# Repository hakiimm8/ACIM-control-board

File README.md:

# ACIM-control-board
 AC induction motor control board

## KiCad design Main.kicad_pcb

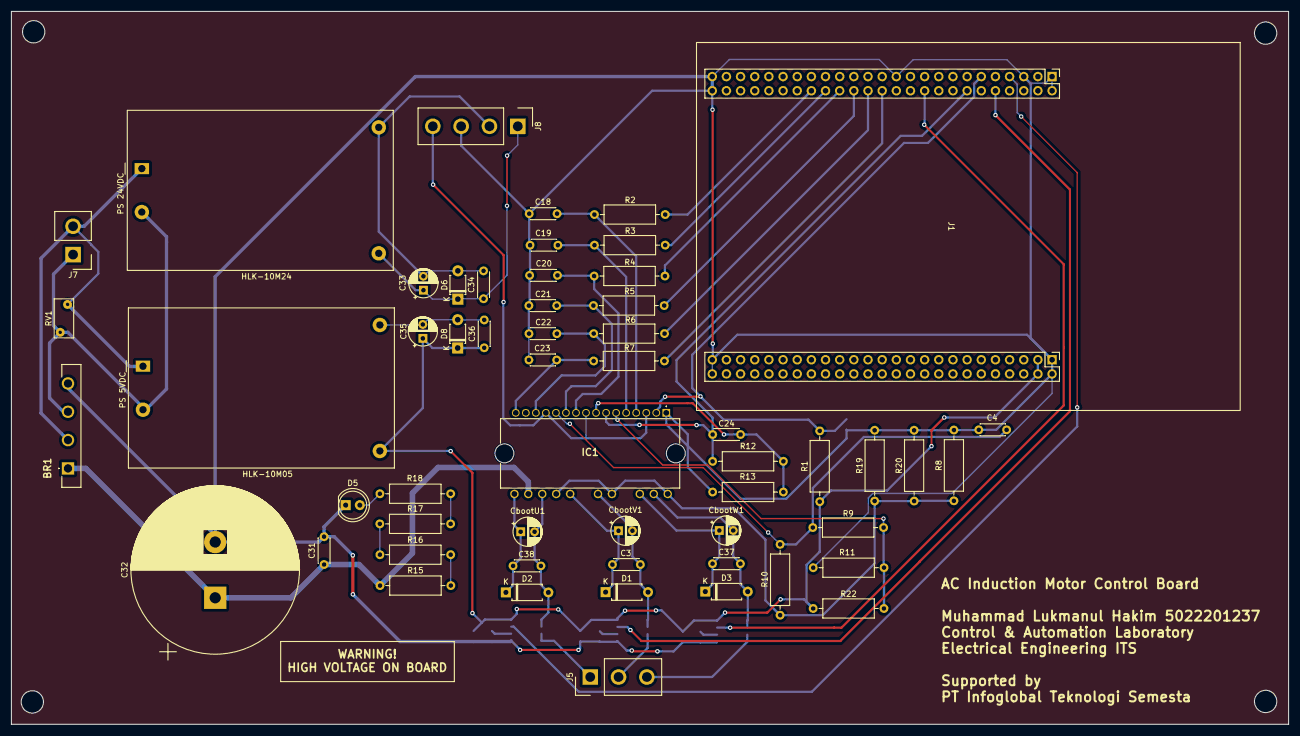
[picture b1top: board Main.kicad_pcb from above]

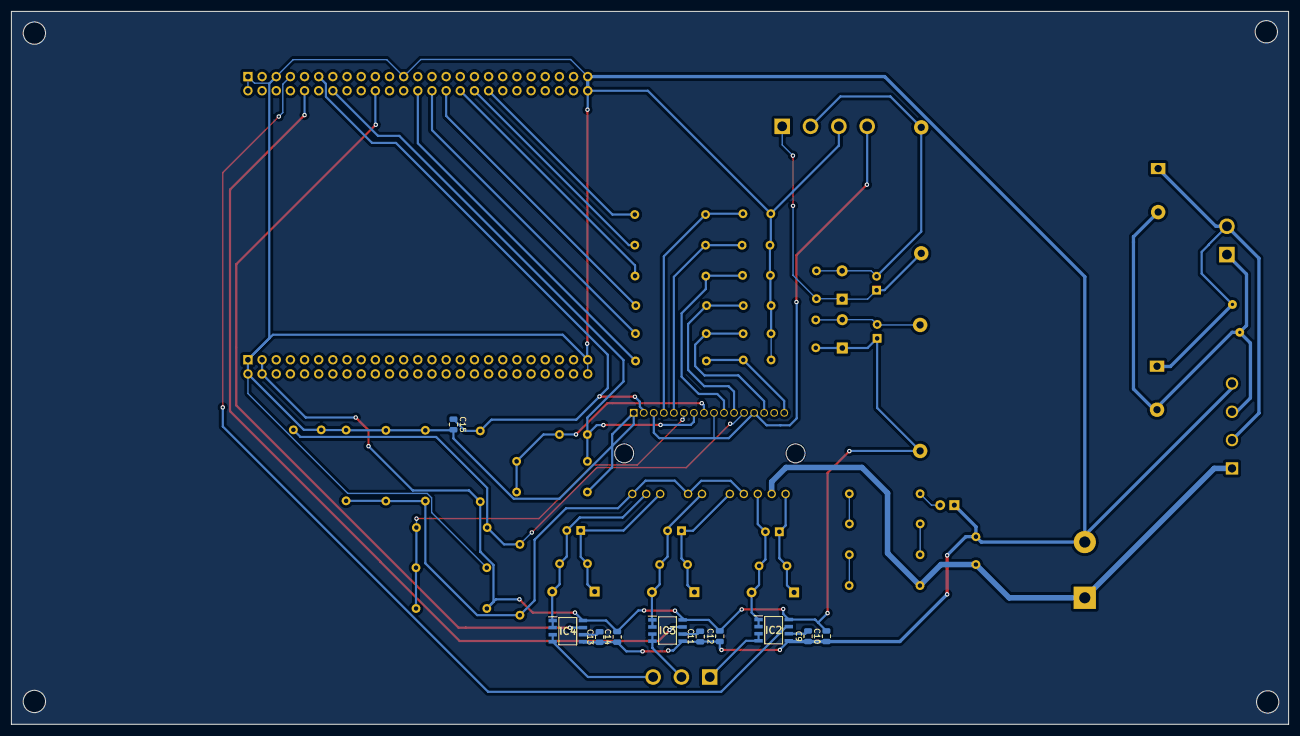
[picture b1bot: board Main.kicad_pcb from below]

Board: 2 copper layers, 229.1 x 127.9 mm, 65 parts (10 on the bottom side), 46 nets.

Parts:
BR1: GBUE2560-M3_P; GBUE2560M3P
C3, C37, C38: 100n; C_Disc_D4.3mm_W1.9mm_P5.00mm
C4: 1nF; C_Disc_D4.3mm_W1.9mm_P5.00mm
C9, C11, C13, C15: 1nF; C_0805_2012Metric
C10, C12, C14: 0.1uF; C_0805_2012Metric
C18, C19, C20, C21, C22, C23: 10pF; C_Disc_D4.3mm_W1.9mm_P5.00mm
C24: 33pF; C_Disc_D4.3mm_W1.9mm_P5.00mm
C31: 220nF; C_Disc_D4.3mm_W1.9mm_P5.00mm
C32: 330uF 400V; CP_Radial_D30.0mm_P10.00mm_SnapIn
C33, C35: 22uF; CP_Radial_D5.0mm_P2.50mm
C34, C36: 100nF; C_Disc_D4.3mm_W1.9mm_P5.00mm
CbootU1: 2.2u; CP_Radial_D5.0mm_P2.50mm
CbootV1: 2.2u; CP_Radial_D5.0mm_P2.50mm
CbootW1: 2.2u; CP_Radial_D5.0mm_P2.50mm
D1, D2, D3: MMSZ5250B; D_A-405_P7.62mm_Horizontal
D5: LED; LED_D5.0mm
D6: DZ24V; D_T-1_P5.08mm_Horizontal
D8: DZ5V; D_T-1_P5.08mm_Horizontal
IC1: STGIPQ3H60T-HL; STGIPQ3H60THL
IC2, IC3, IC4: ACS724LLCTR-05AU-T; SOIC127P600X175-8N
J1: STM32F407G-DISC1-SHIELD
J5: OUT; Samtec_HPM-03-01-x-S_Straight_1x03_Pitch5.08mm
J7: AC_IN; Samtec_HPM-02-01-x-S_Straight_1x02_Pitch5.08mm
J8: Conn_01x04; Samtec_HPM-04-01-x-S_Straight_1x04_Pitch5.08mm
PS 5VDC: HLK-10M05; Converter_ACDC_HiLink_HLK-10Mxx
PS 24VDC: HLK-10M24; Converter_ACDC_HiLink_HLK-10Mxx
R1: 2.2K; R_Axial_DIN0309_L9.0mm_D3.2mm_P12.70mm_Horizontal
R2, R3, R4, R5, R6, R7: 1K; R_Axial_DIN0309_L9.0mm_D3.2mm_P12.70mm_Horizontal
R8, R19, R20: 1R; R_Axial_DIN0309_L9.0mm_D3.2mm_P12.70mm_Horizontal
R9, R10, R11, R13, R22: 3.3K; R_Axial_DIN0309_L9.0mm_D3.2mm_P12.70mm_Horizontal
R12, R15, R16, R17, R18: 10K; R_Axial_DIN0309_L9.0mm_D3.2mm_P12.70mm_Horizontal
RV1: Varistor; RV_Disc_D7mm_W3.5mm_P5mm

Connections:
+5V: C10.2, C12.2, C14.2, C35.1, C36.1, D8.1 (K), IC2.8 (VCC), IC3.8 (VCC), IC4.8 (VCC), J1.53 (5V), J1.54 (5V), PS 5VDC.4 (+Vout), R1.1, R22.1
+15V: IC1.3 (VCC_W_), IC1.9 (VCC_V), IC1.13 (VCC_U), J8.4
+24V: C33.1, C34.1, D6.1 (K), J8.1, PS 24VDC.4 (+Vout)
/Inverter/ADC: C24.1, IC1.7 (OPOUT), J1.14 (PA2), R12.1
/Inverter/CURR_U: IC2.7 (VIOUT), J1.7 (PC1)
/Inverter/CURR_V: IC3.7 (VIOUT), J1.10 (PC2)
/Inverter/CURR_W: IC4.7 (VIOUT), J1.20 (PC4)
/Inverter/HIN_U: J1.28 (PE10), R6.1
/Inverter/HIN_V: J1.32 (PE14), R4.1
/Inverter/HIN_W: J1.36 (PB12), R2.1
/Inverter/HV: BR1.1 (+), C31.1, C32.1, IC1.18, R15.1
/Inverter/LIN_U: J1.26 (PE8), R7.1
/Inverter/LIN_V: J1.30 (PE12), R5.1
/Inverter/LIN_W: J1.34 (PB10), R3.1
/Inverter/NTC: C15.1, IC1.2 (T/~SD/OD_), J1.11 (PA1), R1.2
/Inverter/U: IC2.3 (IP-_1), IC2.4 (IP-_2), J5.1
/Inverter/V: IC3.3 (IP-_1), IC3.4 (IP-_2), J5.2
/Inverter/W: IC4.3 (IP-_1), IC4.4 (IP-_2), J5.3
/Rectifier & Power supply/L: BR1.2 (~_1), J7.2, PS 5VDC.1 (AC/L), PS 24VDC.1 (AC/L), RV1.1
/Rectifier & Power supply/N: BR1.3 (~_2), J7.1, PS 5VDC.2 (AC/N), PS 24VDC.2 (AC/N), RV1.2
GND: BR1.4 (-), C4.2, C9.1, C10.1, C11.1, C12.1, C13.1, C14.1, C15.2, C18.2, C19.2, C20.2, C21.2, C22.2, C23.2, C31.2, C32.2, D5.1 (K), IC1.1 (GND), IC2.5 (GND), IC3.5 (GND), IC4.5 (GND), J1.1 (GND), J1.2 (GND), J1.5 (GND), J1.23 (GND), J1.49 (GND), J1.50 (GND), J1.51 (GND), J1.52 (GND), J1.99 (GND), J1.100 (GND), J8.3, R8.2, R11.2, R13.2, R19.2, R20.2
unnamed: C3.1, CbootV1.2, D1.2 (A), IC1.22 (V_OUTV), IC3.1 (IP+_1), IC3.2 (IP+_2)
unnamed: C3.2, CbootV1.1, D1.1 (K), IC1.21 (VBOOT_V)
unnamed: C38.1, CbootU1.2, D2.2 (A), IC1.19 (U_OUTU), IC2.1 (IP+_1), IC2.2 (IP+_2)
unnamed: C38.2, CbootU1.1, D2.1 (K), IC1.17 (VBOOT_U)
unnamed: C37.1, CbootW1.2, D3.2 (A), IC1.25 (W_OUTW), IC4.1 (IP+_1), IC4.2 (IP+_2)
unnamed: C37.2, CbootW1.1, D3.1 (K), IC1.24 (VBOOT_W)
unnamed: D5.2 (A), R18.2
unnamed: C33.2, C34.2, D6.2 (A), J8.2, PS 24VDC.3 (-Vout)
unnamed: C35.2, C36.2, D8.2 (A), PS 5VDC.3 (-Vout)
unnamed: C22.1, IC1.14 (HIN_U), R6.2
unnamed: C20.1, IC1.10 (HIN_V_), R4.2
unnamed: C18.1, IC1.4 (HIN_W), R2.2
unnamed: C23.1, IC1.16 (LIN_U), R7.2
unnamed: C21.1, IC1.11 (LIN_V), R5.2
unnamed: C19.1, IC1.5 (LIN_W), R3.2
unnamed: IC1.20 (NU), IC1.23 (NV), IC1.26 (NW), R8.1, R10.2, R19.1, R20.1
unnamed: IC1.6 (OP+), R9.2, R11.1, R22.2
unnamed: C24.2, IC1.8 (OP-), R12.2, R13.1
unnamed: C9.2, IC2.6 (FILTER)
unnamed: C11.2, IC3.6 (FILTER)
unnamed: C13.2, IC4.6 (FILTER)
unnamed: R15.2, R16.1
unnamed: R16.2, R17.1
unnamed: R17.2, R18.1
RS: C4.1, IC1.12 (CIN_), R9.1, R10.1

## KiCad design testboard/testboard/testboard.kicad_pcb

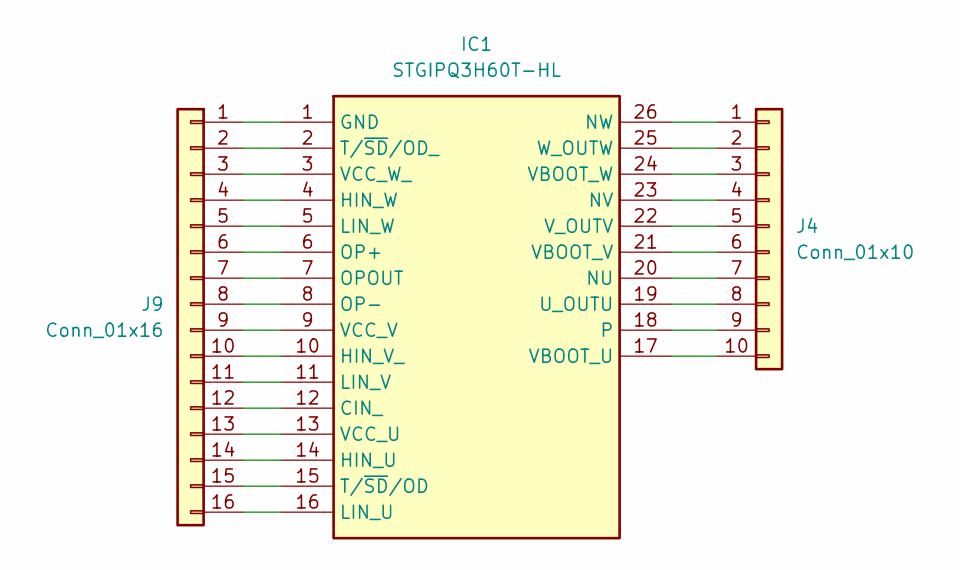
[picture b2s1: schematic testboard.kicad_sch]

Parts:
IC1: STGIPQ3H60T-HL; STGIPQ3H60THL; Manufacturer_Part_Number STGIPQ3H60T-HL; Mouser Part Number 511-STGIPQ3H60T-HL
J4: Conn_01x10; Samtec_HPM-10-01-x-S_Straight_1x10_Pitch5.08mm
J9: Conn_01x16; PinHeader_1x16_P2.54mm_Vertical

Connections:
unnamed: IC1.12 (CIN_), J9.12
unnamed: IC1.1 (GND), J9.1
unnamed: IC1.14 (HIN_U), J9.14
unnamed: IC1.10 (HIN_V_), J9.10
unnamed: IC1.4 (HIN_W), J9.4
unnamed: IC1.16 (LIN_U), J9.16
unnamed: IC1.11 (LIN_V), J9.11
unnamed: IC1.5 (LIN_W), J9.5
unnamed: IC1.20 (NU), J4.7
unnamed: IC1.23 (NV), J4.4
unnamed: IC1.26 (NW), J4.1
unnamed: IC1.6 (OP+), J9.6
unnamed: IC1.8 (OP-), J9.8
unnamed: IC1.7 (OPOUT), J9.7
unnamed: IC1.18, J4.9
unnamed: IC1.15 (T/~SD/OD), J9.15
unnamed: IC1.2 (T/~SD/OD_), J9.2
unnamed: IC1.19 (U_OUTU), J4.8
unnamed: IC1.17 (VBOOT_U), J4.10
unnamed: IC1.21 (VBOOT_V), J4.6
unnamed: IC1.24 (VBOOT_W), J4.3
unnamed: IC1.13 (VCC_U), J9.13
unnamed: IC1.9 (VCC_V), J9.9
unnamed: IC1.3 (VCC_W_), J9.3
unnamed: IC1.22 (V_OUTV), J4.5
unnamed: IC1.25 (W_OUTW), J4.2

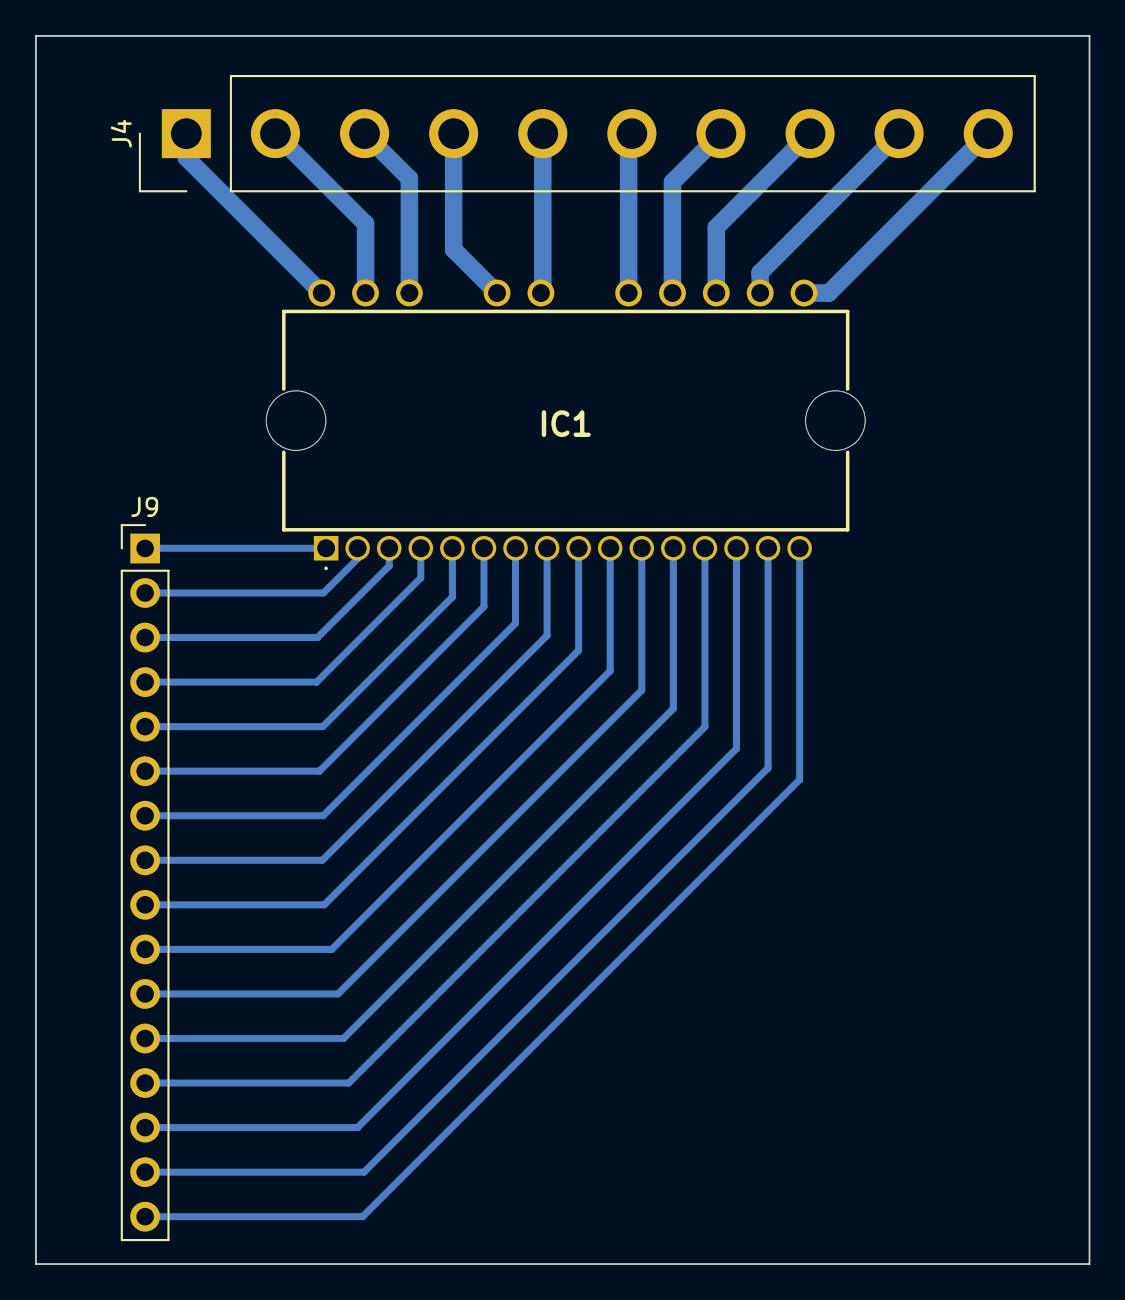
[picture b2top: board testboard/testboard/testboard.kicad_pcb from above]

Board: 2 copper layers, 60.1 x 70.0 mm, 3 parts (0 on the bottom side), 26 nets.

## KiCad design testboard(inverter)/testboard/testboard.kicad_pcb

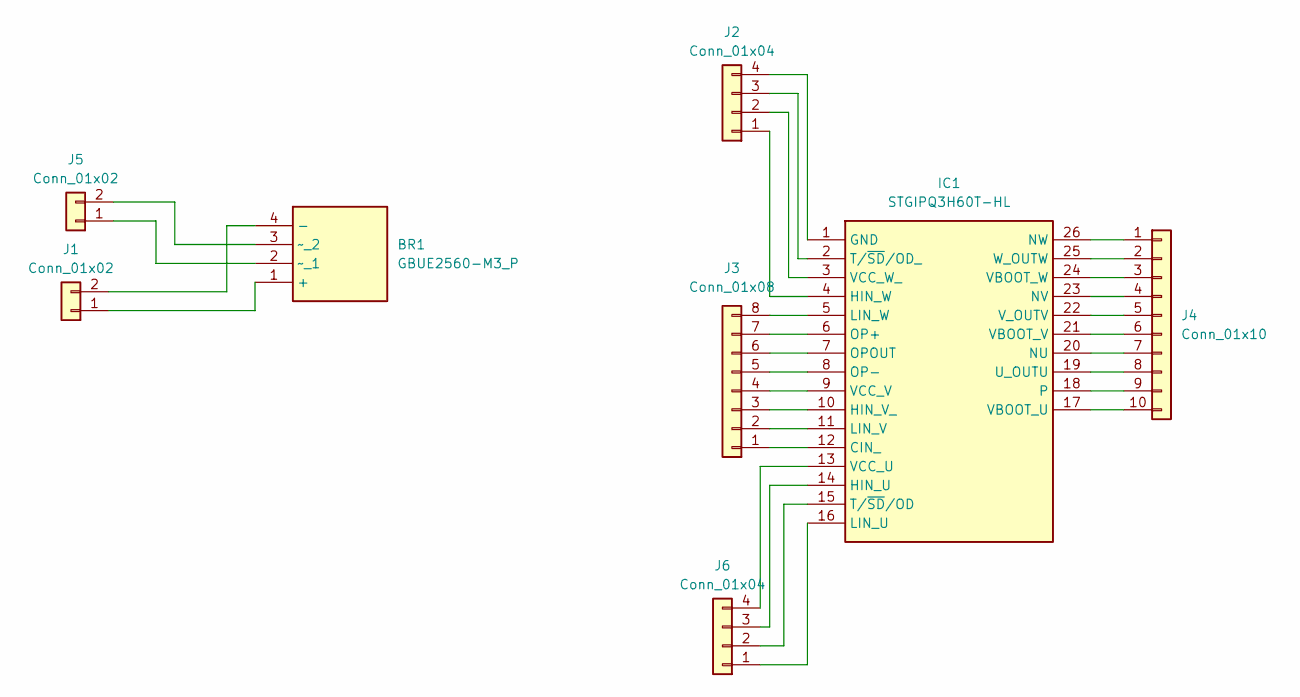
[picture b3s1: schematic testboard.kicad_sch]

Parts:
BR1: GBUE2560-M3_P; GBUE2560M3P; Manufacturer_Part_Number GBUE2560-M3/P; Mouser Part Number 78-GBUE2560-M3/P
IC1: STGIPQ3H60T-HL; STGIPQ3H60THL; Manufacturer_Part_Number STGIPQ3H60T-HL; Mouser Part Number 511-STGIPQ3H60T-HL
J1, J5: Conn_01x02; Samtec_HPM-02-01-x-S_Straight_1x02_Pitch5.08mm
J2, J6: Conn_01x04; Samtec_HPM-04-01-x-S_Straight_1x04_Pitch5.08mm
J3: Conn_01x08; Samtec_HPM-08-01-x-S_Straight_1x08_Pitch5.08mm
J4: Conn_01x10; Samtec_HPM-10-01-x-S_Straight_1x10_Pitch5.08mm

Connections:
unnamed: BR1.1 (+), J1.1
unnamed: BR1.4 (-), J1.2
unnamed: BR1.2 (~_1), J5.1
unnamed: BR1.3 (~_2), J5.2
unnamed: IC1.12 (CIN_), J3.1
unnamed: IC1.1 (GND), J2.4
unnamed: IC1.14 (HIN_U), J6.3
unnamed: IC1.10 (HIN_V_), J3.3
unnamed: IC1.4 (HIN_W), J2.1
unnamed: IC1.16 (LIN_U), J6.1
unnamed: IC1.11 (LIN_V), J3.2
unnamed: IC1.5 (LIN_W), J3.8
unnamed: IC1.20 (NU), J4.7
unnamed: IC1.23 (NV), J4.4
unnamed: IC1.26 (NW), J4.1
unnamed: IC1.6 (OP+), J3.7
unnamed: IC1.8 (OP-), J3.5
unnamed: IC1.7 (OPOUT), J3.6
unnamed: IC1.18, J4.9
unnamed: IC1.15 (T/~SD/OD), J6.2
unnamed: IC1.2 (T/~SD/OD_), J2.3
unnamed: IC1.19 (U_OUTU), J4.8
unnamed: IC1.17 (VBOOT_U), J4.10
unnamed: IC1.21 (VBOOT_V), J4.6
unnamed: IC1.24 (VBOOT_W), J4.3
unnamed: IC1.13 (VCC_U), J6.4
unnamed: IC1.9 (VCC_V), J3.4
unnamed: IC1.3 (VCC_W_), J2.2
unnamed: IC1.22 (V_OUTV), J4.5
unnamed: IC1.25 (W_OUTW), J4.2

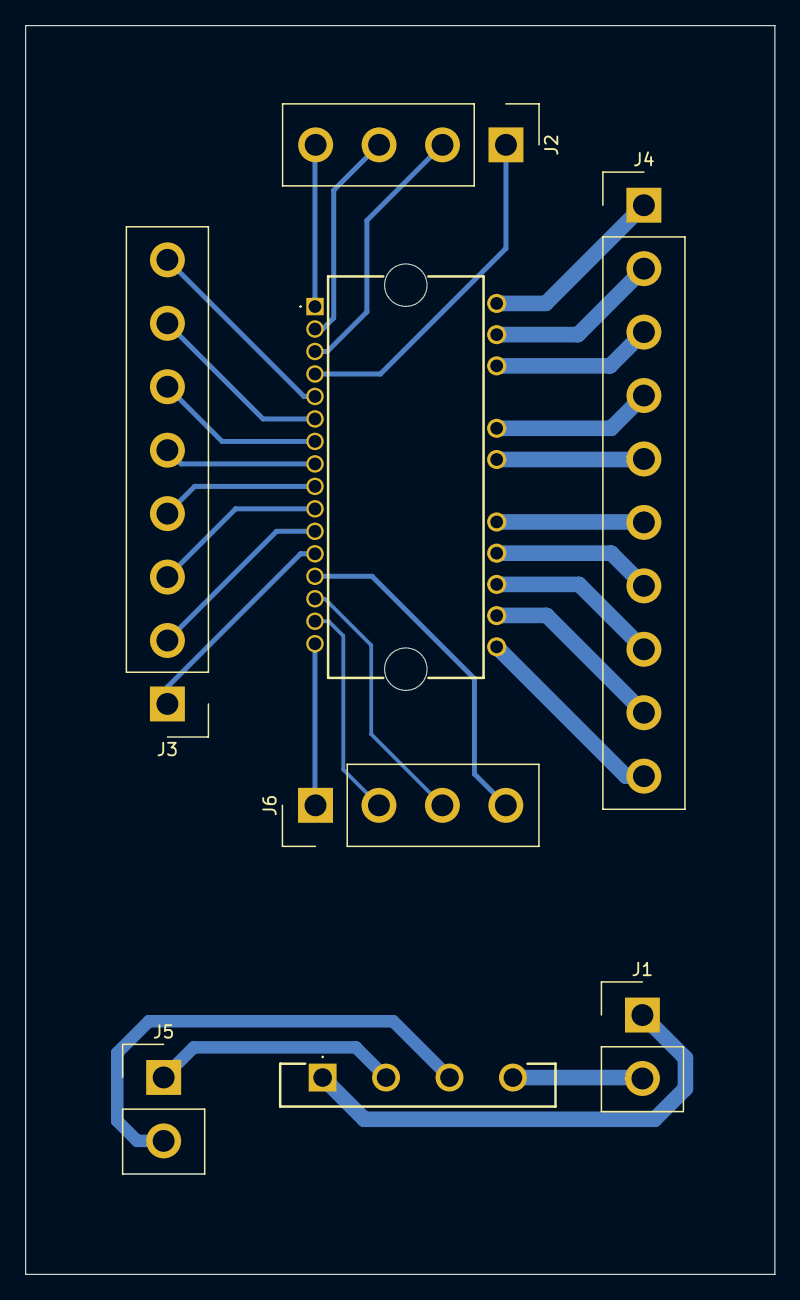
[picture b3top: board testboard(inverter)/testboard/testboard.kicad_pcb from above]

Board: 2 copper layers, 60.0 x 100.0 mm, 8 parts (0 on the bottom side), 30 nets.

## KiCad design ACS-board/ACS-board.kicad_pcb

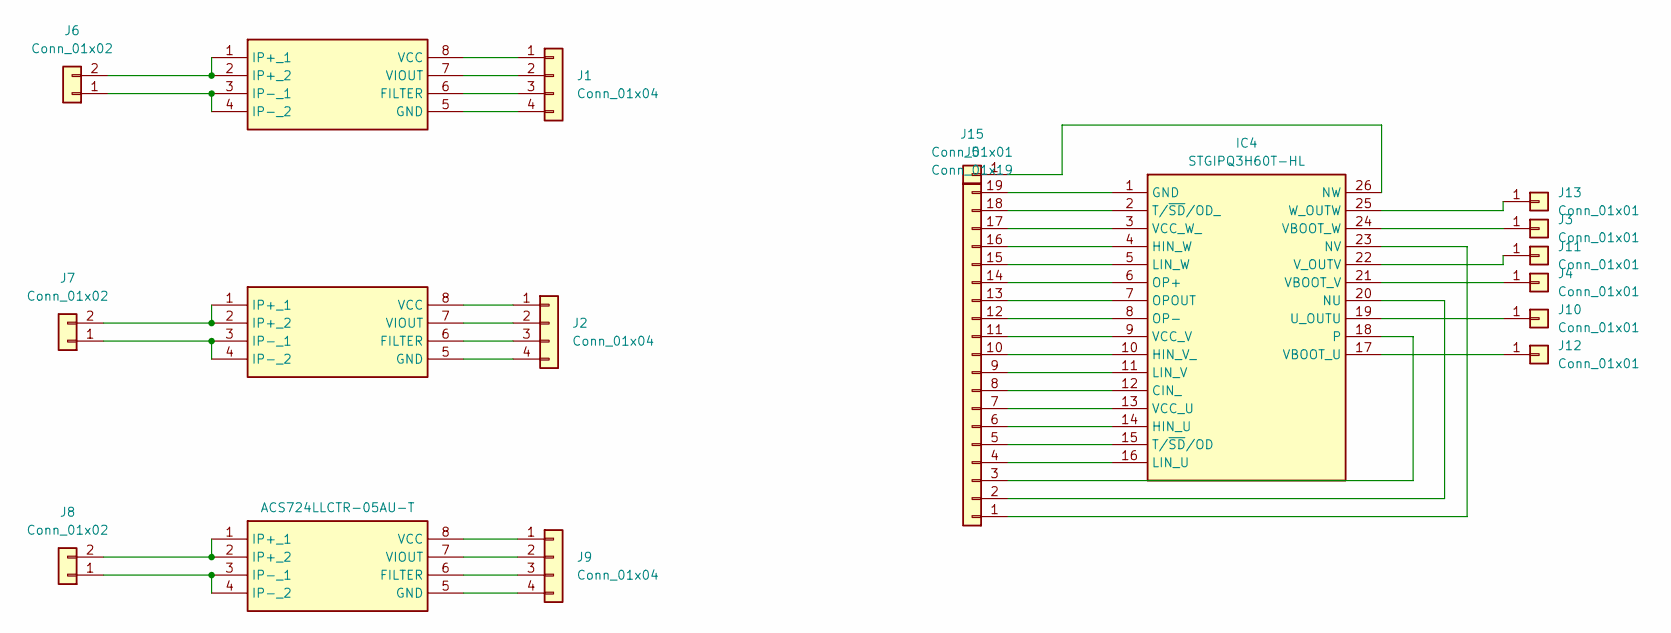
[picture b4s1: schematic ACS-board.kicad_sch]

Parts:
IC1, IC2, IC3: ACS724LLCTR-05AU-T; SOIC127P600X175-8N; Manufacturer_Part_Number ACS724LLCTR-05AU-T; Mouser Part Number 250-724LLCTR05AUT
IC4: STGIPQ3H60T-HL; STGIPQ3H60THL; Manufacturer_Part_Number STGIPQ3H60T-HL; Mouser Part Number 511-STGIPQ3H60T-HL
J1, J2, J9: Conn_01x04; PinHeader_1x04_P2.54mm_Vertical
J3, J4, J10, J11, J12, J13: Conn_01x01; PinHeader_1x01_P2.54mm_Vertical
J5: Conn_01x19; Samtec_HPM-19-01-x-S_Straight_1x19_Pitch5.08mm
J6, J7, J8: Conn_01x02; Samtec_HPM-02-01-x-S_Straight_1x02_Pitch5.08mm
J15: Conn_01x01; Samtec_HPM-01-01-x-S_Straight_1x01_Pitch5.08mm

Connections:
unnamed: IC1.6 (FILTER), J1.3
unnamed: IC1.5 (GND), J1.4
unnamed: IC1.1 (IP+_1), IC1.2 (IP+_2), J6.2
unnamed: IC1.3 (IP-_1), IC1.4 (IP-_2), J6.1
unnamed: IC1.8 (VCC), J1.1
unnamed: IC1.7 (VIOUT), J1.2
unnamed: IC2.6 (FILTER), J2.3
unnamed: IC2.5 (GND), J2.4
unnamed: IC2.1 (IP+_1), IC2.2 (IP+_2), J7.2
unnamed: IC2.3 (IP-_1), IC2.4 (IP-_2), J7.1
unnamed: IC2.8 (VCC), J2.1
unnamed: IC2.7 (VIOUT), J2.2
unnamed: IC3.6 (FILTER), J9.3
unnamed: IC3.5 (GND), J9.4
unnamed: IC3.1 (IP+_1), IC3.2 (IP+_2), J8.2
unnamed: IC3.3 (IP-_1), IC3.4 (IP-_2), J8.1
unnamed: IC3.8 (VCC), J9.1
unnamed: IC3.7 (VIOUT), J9.2
unnamed: IC4.12 (CIN_), J5.8
unnamed: IC4.1 (GND), J5.19
unnamed: IC4.14 (HIN_U), J5.6
unnamed: IC4.10 (HIN_V_), J5.10
unnamed: IC4.4 (HIN_W), J5.16
unnamed: IC4.16 (LIN_U), J5.4
unnamed: IC4.11 (LIN_V), J5.9
unnamed: IC4.5 (LIN_W), J5.15
unnamed: IC4.20 (NU), J5.2
unnamed: IC4.23 (NV), J5.1
unnamed: IC4.26 (NW), J15.1
unnamed: IC4.6 (OP+), J5.14
unnamed: IC4.8 (OP-), J5.12
unnamed: IC4.7 (OPOUT), J5.13
unnamed: IC4.18, J5.3
unnamed: IC4.15 (T/~SD/OD), J5.5
unnamed: IC4.2 (T/~SD/OD_), J5.18
unnamed: IC4.19 (U_OUTU), J10.1
unnamed: IC4.17 (VBOOT_U), J12.1
unnamed: IC4.21 (VBOOT_V), J4.1
unnamed: IC4.24 (VBOOT_W), J3.1
unnamed: IC4.13 (VCC_U), J5.7
unnamed: IC4.9 (VCC_V), J5.11
unnamed: IC4.3 (VCC_W_), J5.17
unnamed: IC4.22 (V_OUTV), J11.1
unnamed: IC4.25 (W_OUTW), J13.1

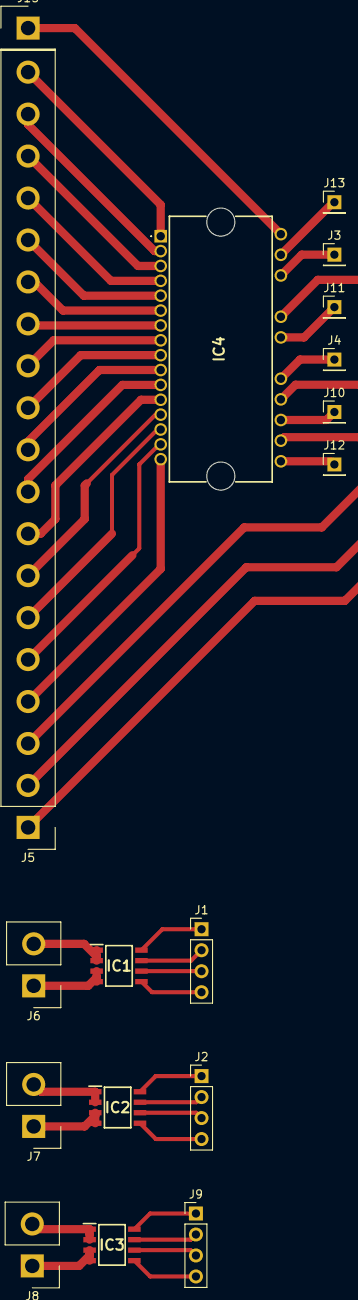
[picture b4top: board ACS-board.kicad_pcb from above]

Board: 2 copper layers, 18 parts (0 on the bottom side), 44 nets.

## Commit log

2023-10-20 update description & value
2023-10-22 update power supply page
2023-10-25 update power label
2023-10-25 adding high speed isolator
2023-12-28 updating component & board
2024-01-07 update testboard
2024-01-08 update footprint
2024-01-09 update schematics, BOM, & test board
2024-01-12 simplifies the schematics according to the local provider & assign footprint
2024-01-13 add overcurrent protection
2024-01-14 update schematics
2024-01-16 pcb layout design
2024-01-17 add copper zone, drill mounting, text to the pcb
